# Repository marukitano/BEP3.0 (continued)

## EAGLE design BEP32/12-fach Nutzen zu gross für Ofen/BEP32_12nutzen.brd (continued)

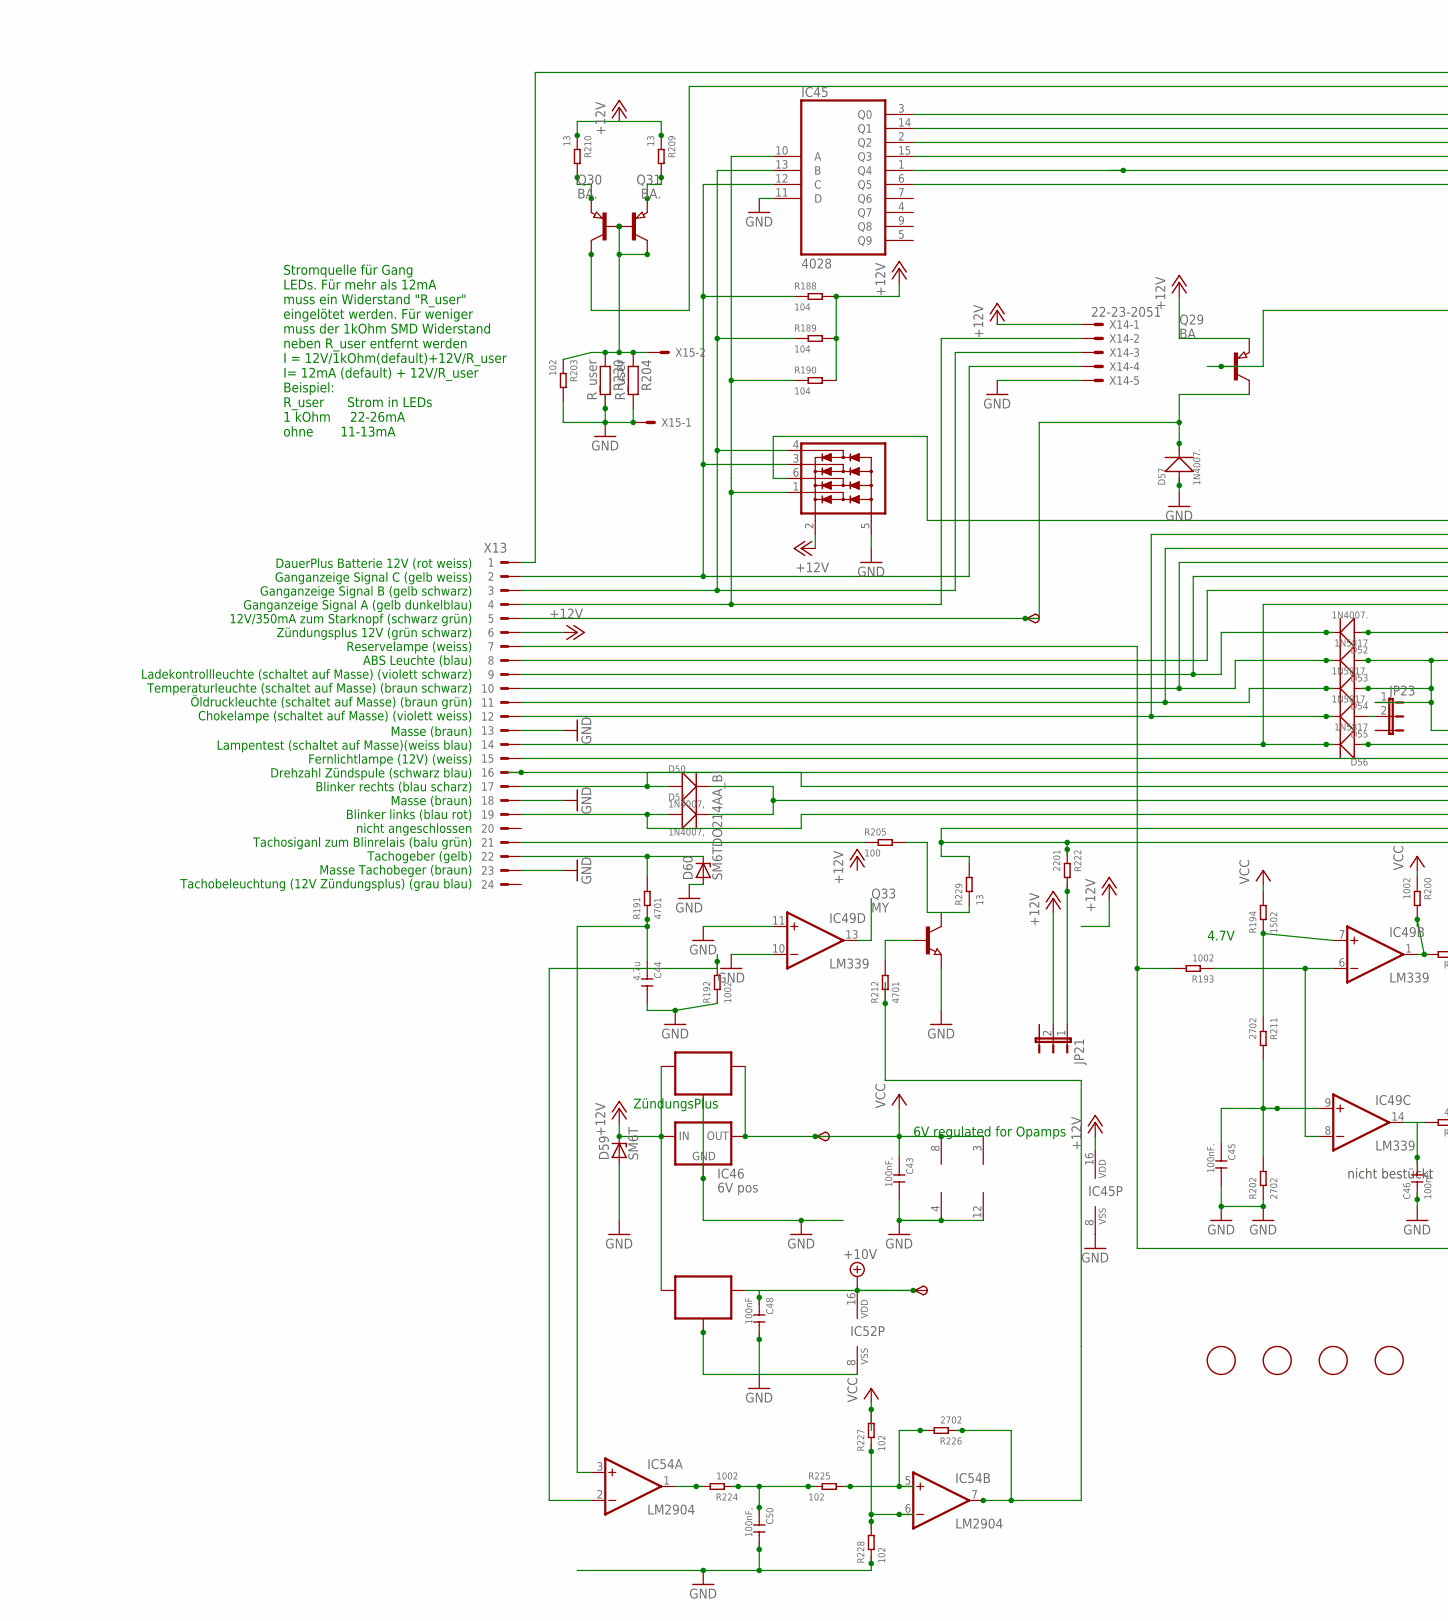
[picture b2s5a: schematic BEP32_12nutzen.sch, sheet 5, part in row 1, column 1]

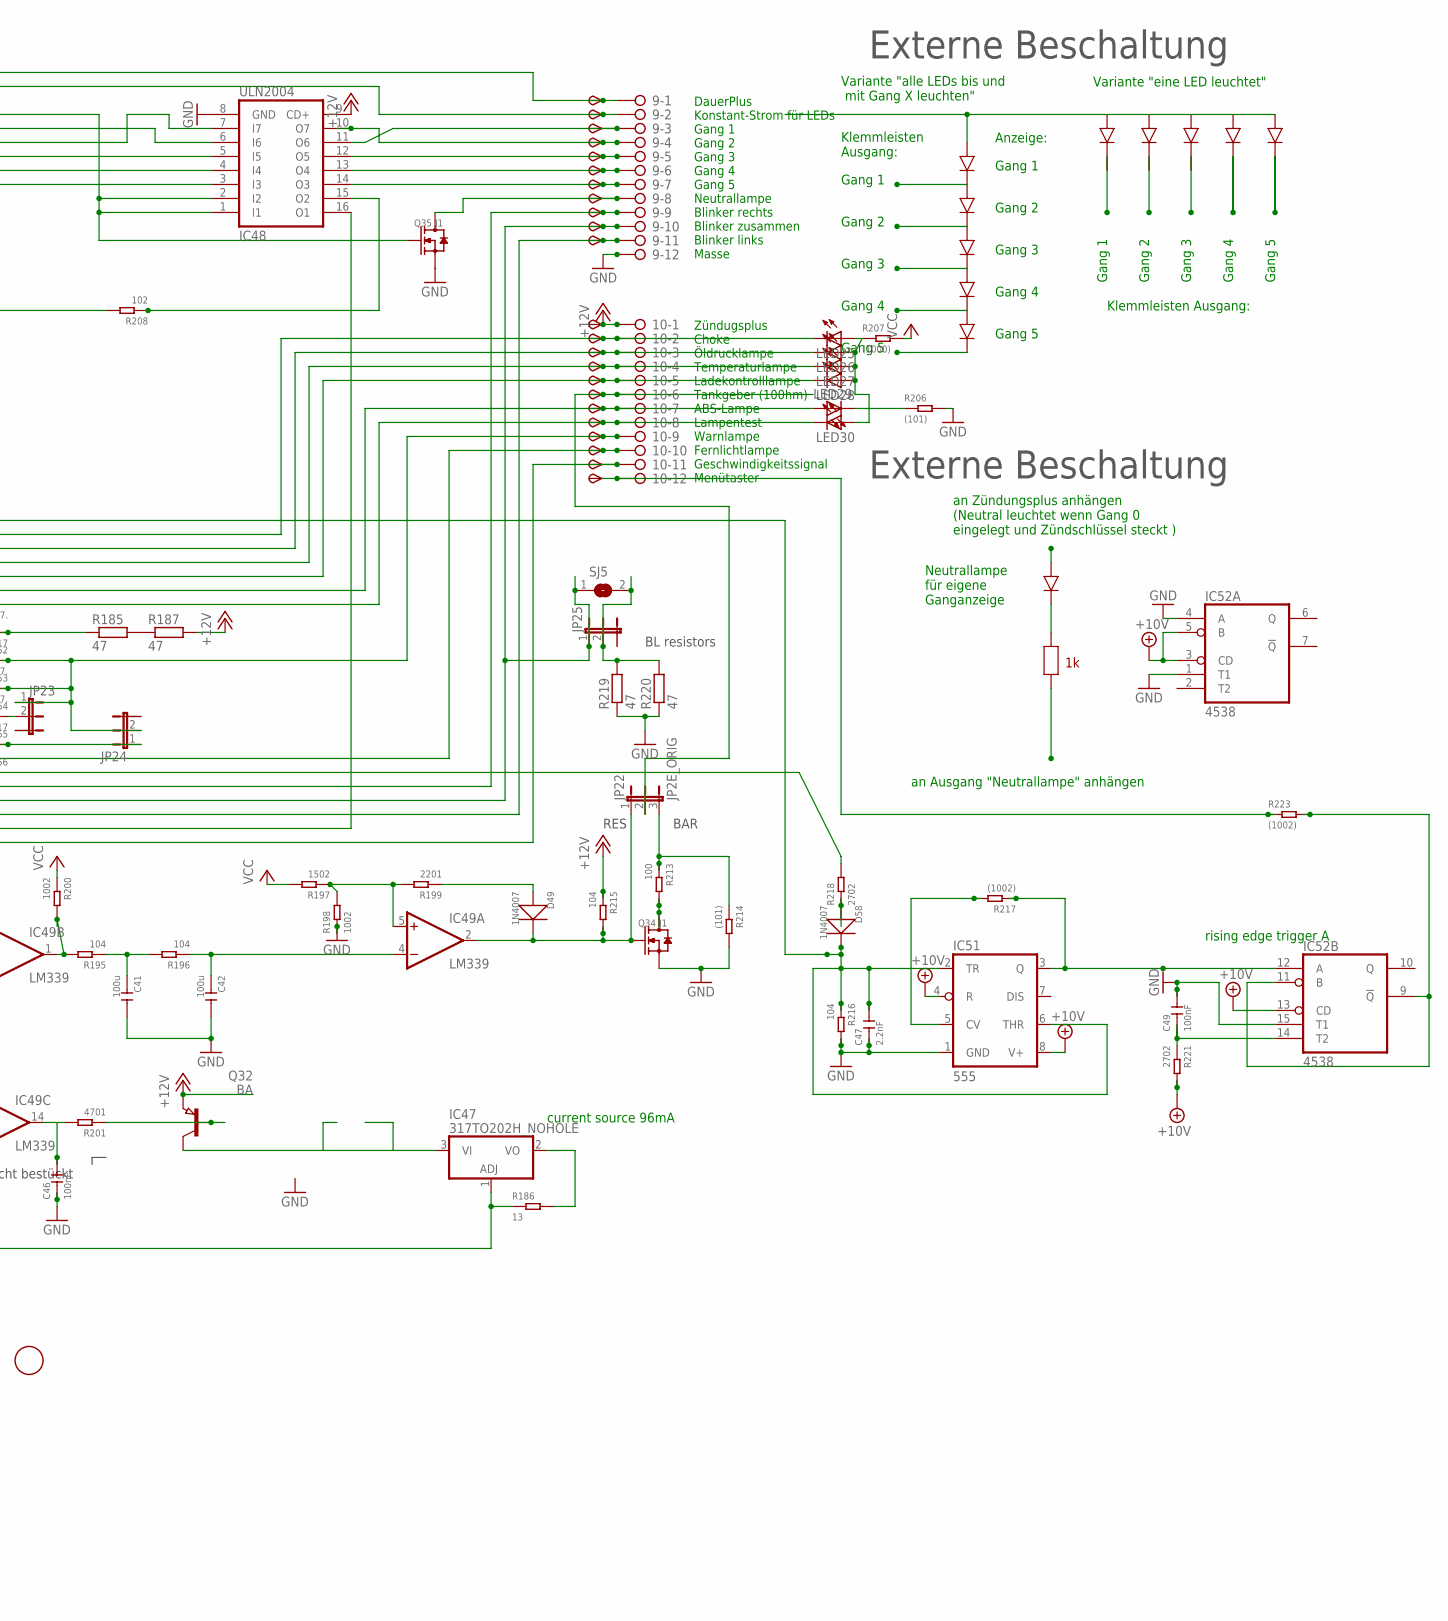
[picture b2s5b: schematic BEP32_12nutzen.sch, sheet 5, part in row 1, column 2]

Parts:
6V4, 10V4: TPSB2.0; B2.0
9, 10: 2081-1132; 12-PIN
C41, C42: 100u; C1206
C43, C50: 100nF,; C0805
C44: 4.7u; C0805
C45, C46: 100nF.; C0805
C47: 2.2nF; C0805
C48, C49: 100nF; C0805
D49, D58: 1N4007; DO-214AC
D50, D51: 1N4007,; DO-214AC
D52, D57: 1N4007.; DO-214AC
D53, D56: 1N5817; DO-214AC_SLIM
D54, D55: 1N5817.; DO-214AC_SLIM
D59: SM6T; DO214AA
D60: SM6TDO214AA_BI; DO214AA_BI
FID17, FID18, FID19, FID20: FIDUCIAL; FIDUCIAL_1MM
IC45: 4028; SO16
IC46: 6V pos; 78LXX
IC47: 317TO202H_NOHOLE; TO220H_NOHOLE
IC48: ULN2004; SO16
IC49: LM339; SO14
IC50: 78L06; SOT89_ROUND
IC51: 555; SO08
IC52: 4538; SO16
IC53: 78L10; SOT89_ROUND
IC54: LM2904; SO08
IC55: NUP4304SOT457_R; SOT457R_PHILIPS
JP21, JP23, JP24, JP25: JP2EJP2_SMALLPADS; JP2_SMALLPADS
JP22: JP2E_ORIG; JP2_ORIG_SMALLPADS
LED25, LED26, LED27, LED28, LED29, LED30: LEDLD260; LD260
Q29, Q32: BA; SOT89
Q30, Q31: BA.; SOT89
Q33: MY; SOT89
Q34, Q35: J1; SOT-23
R185, R187, R219, R220: 47; V235/17_1MM
R186, R209, R210, R229: 13; R1206
R188, R189, R190, R195, R196, R215, R216: 104; R0805
R191, R201, R212: 4701; R0805
R192, R193, R198, R200, R224: 1002; R0805
R194, R197: 1502; R0805
R199, R222: 2201; R0805
R202, R211, R218, R221, R226: 2702; R0805
R203, R208, R225, R227, R228: 102; R0805
R204, R230: R_user; R0805
R205, R213: 100; R0805
R206, R214: (101); R0805
R207: (1000); R0805
R217, R223: (1002); R0805
SJ5: SJ
START4: TPSB2.0; B2.0
TP93, TP94, TP95, TP96, TP97, TP98, TP99, TP100, TP101, TP102, TP103, TP104, TP105, TP106, TP107, TP108, TP109, TP110, TP112, TP113, TP114, TP115: TPSB2.0; B2.0
TP111: TPSB1,27; B1,27
X13: CON_BMWV2; 24-PIN_V2
X14: 22-23-2051
X15: 22-23-2021

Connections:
+10V: 10V4.TP, C48.1, IC51.4 (R), IC51.8 (V+), IC52.3 (CD), IC52.5 (B), IC52.13 (CD), IC52.16 (VDD), IC53.1 (OUT), R221.2; also elsewhere on the board
+12V: 10.1, D59.C, IC45.16 (VDD), IC46.IN, IC48.9 (CD+), IC50.3 (IN), IC53.3 (IN), IC55.2 (V+), JP21.2, Q29.3 (E), Q32.3 (E), R187.2, R188.2, R189.2, R190.2, R209.1, R210.1, R215.1, TP114.TP, X13.6, X14.1; also elsewhere on the board
+12V5: IC54.7 (OUT), R212.1, R226.1
GND: 9.12, C41.2, C42.2, C43.2, C44.2, C45.2, C46.1, C47.1, C48.2, C49.2, C50.2, D57.1 (+), D59.A, D60.A, IC45.8 (VSS), IC45.11 (D), IC46.GND, IC48.8 (GND), IC49.10 (-IN), IC49.11 (+IN), IC49.12 (GND), IC50.2 (GND), IC50.2@1 (GND), IC51.1 (GND), IC52.1 (T1), IC52.4 (A), IC52.8 (VSS), IC52.15 (T1), IC53.2 (GND), IC53.2@1 (GND), IC54.4 (V-), IC55.5 (V-), Q33.3 (E), Q34.2 (S), Q35.2 (S), R192.1, R198.1, R202.1, R203.2, R204.2, R206.2, R214.2, R216.2, R219.1, R220.1, R228.1, R230.2, X13.13, X13.18, X13.23, X14.5, X15.1; also elsewhere on the board
unnamed: R185.2, R187.1
unnamed: 10.9, D53.1 (+), D54.1 (+), JP23.1, JP24.2, TP111.TP
unnamed: IC45.10 (A), IC55.1 (D1), R190.1, X13.4, X14.2
unnamed: IC45.13 (B), IC55.4 (D4), R189.1, X13.3, X14.3
unnamed: D57.2 (-), Q29.2 (C), START4.TP, X13.5
unnamed: IC45.12 (C), IC55.3 (D3), R188.1, X13.2, X14.4
unnamed: 10.7, LED29.A, TP109.TP, X13.8
unnamed: 10.2, D55.2 (-), LED25.K (C), TP104.TP, X13.12
unnamed: 10.3, D54.2 (-), LED26.K (C), TP105.TP, X13.11
unnamed: 10.4, D53.2 (-), LED27.K (C), TP106.TP, X13.10
unnamed: 10.8, D56.2 (-), LED30.K (C), TP110.TP, X13.14
unnamed: 9.9, D50.1 (+), TP101.TP, X13.17
unnamed: 9.11, D51.1 (+), TP103.TP, X13.19
unnamed: D60.C, R191.2, X13.22
unnamed: C44.1, IC54.3 (+IN), R191.1
unnamed: 10.11, IC48.16 (O1), R222.1, R229.2, TP113.TP
unnamed: IC49.1 (OUT), R195.2, R200.2
unnamed: C41.1, R195.1, R196.2
unnamed: C42.1, IC49.4 (-IN), R196.1
unnamed: IC49.5 (+IN), R197.1, R198.2, R199.2
unnamed: D49.1 (+), R199.1
unnamed: C45.1, IC49.9 (+IN), R202.2, R211.2
unnamed: C46.2, IC49.14 (OUT), R201.2
unnamed: Q32.1 (B), R201.1
unnamed: IC45.2 (Q2), IC48.7 (I7)
unnamed: 9.5, IC48.12 (O5), TP97.TP
unnamed: IC45.1 (Q4), IC48.4 (I4)
unnamed: 9.8, Q35.3 (D), TP100.TP
unnamed: 10.10, TP112.TP, X13.15
unnamed: 10.5, D52.2 (-), LED28.K (C), TP107.TP, X13.9
unnamed: D52.1 (+), R185.1
unnamed: IC45.6 (Q5), IC48.3 (I3)
unnamed: 9.4, IC48.10 (O7), TP96.TP
unnamed: IC47.1 (ADJ), R186.1, R193.2, X13.7
unnamed: IC49.6 (-IN), IC49.8 (-IN), R193.1
unnamed: 9.2, Q31.2 (C), TP94.TP
unnamed: 9.1, TP93.TP, X13.1
unnamed: R218.2, X13.16
unnamed: IC45.15 (Q3), IC48.5 (I5)
unnamed: 9.6, IC48.13 (O4), TP98.TP
unnamed: 9.7, IC48.14 (O3), TP99.TP
unnamed: 10.6, JP22.2, TP108.TP
unnamed: LED29.K (C), R206.1
unnamed: LED25.A, LED26.A, LED27.A, LED28.A, LED30.A, R207.1
unnamed: Q29.1 (B), R208.2
unnamed: IC45.3 (Q0), IC48.1 (I1), IC48.2 (I2), Q35.1 (G)
unnamed: IC45.14 (Q1), IC48.6 (I6)
unnamed: 9.3, IC48.11 (O6), TP95.TP
unnamed: Q30.1 (B), Q30.2 (C), Q31.1 (B), R203.1, R204.1, R230.1, X15.2
unnamed: Q31.3 (E), R210.2
unnamed: Q30.3 (E), R209.2
unnamed: IC49.7 (+IN), R194.1, R211.1
unnamed: IC54.2 (-IN), R192.2
unnamed: Q33.1 (B), R212.2
unnamed: Q34.3 (D), R213.2
unnamed: IC47.2 (VO), R186.2
unnamed: IC47.3 (VI), Q32.2 (C)
unnamed: C47.2, D58.2 (-), IC51.2 (TR), IC51.6 (THR), IC55.6 (D2), R216.1
unnamed: IC51.5 (CV), R217.2
unnamed: IC51.3 (Q), IC52.12 (A), R217.1
unnamed: D58.1 (+), R218.1
unnamed: 9.10, D50.2 (-), D51.2 (-), JP25.1, SJ5.1, TP102.TP
unnamed: JP25.2, R219.2, R220.2, SJ5.2
unnamed: IC52.9 (!Q), IC52.11 (B), R223.2
unnamed: C49.1, IC52.14 (T2), R221.1
unnamed: JP21.1, R222.2
unnamed: IC48.15 (O2), R208.1
unnamed: 10.12, R223.1, TP115.TP
unnamed: D55.1 (+), JP23.2
unnamed: D49.2 (-), IC49.2 (OUT), JP22.1, Q34.1 (G), R215.2
unnamed: IC54.1 (OUT), R224.2
unnamed: C50.1, R224.1, R225.1
unnamed: IC54.5 (+IN), R225.2, R226.2
unnamed: IC54.6 (-IN), R227.1, R228.2
unnamed: D56.1 (+), JP24.1
unnamed: JP22.3, R213.1, R214.1
unnamed: R205.1, X13.21
unnamed: Q33.2 (C), R205.2, R229.1
VCC: 6V4.TP, C43.1, IC46.OUT, IC49.3 (V+), IC50.1 (OUT), IC54.8 (V+), R194.2, R197.2, R200.1, R207.2, R227.2; also elsewhere on the board

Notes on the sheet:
6V regulated for Opamps
current source 96mA
ZündungsPlus
Zündugsplus Choke Öldrucklampe Temperaturlampe Ladekontrolllampe Tankgeber (100hm) ABS-Lampe Lampentest Warnlampe Fernlichtlampe Geschwindigkeitssignal Menütaster
DauerPlus Konstant-Strom für LEDs Gang 1 Gang 2 Gang 3 Gang 4 Gang 5 Neutrallampe Blinker rechts Blinker zusammen Blinker links Masse
DauerPlus Batterie 12V (rot weiss) Ganganzeige Signal C (gelb weiss) Ganganzeige Signal B (gelb schwarz) Ganganzeige Signal A (gelb dunkelblau) 12V/350mA zum Starknopf (schwarz grün) Zündungsplus 12V (grün schwarz) Reservelampe (weiss) ABS Leuchte (blau) Ladekontrollleuchte (schaltet auf Masse) (vi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
Masse (braun) Lampentest (schaltet auf Masse)(weiss blau) Fernlichtlampe (12V) (weiss) Drehzahl Zündspule (schwarz blau) Blinker rechts (blau scharz) Masse (braun) Blinker links (blau rot) nicht angeschlossen Tachosiganl zum Blinrelais (balu grün) Tachogeber (gelb) Masse Tachobeger (braun) Tachobel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
4.7V
Stromquelle für Gang LEDs. Für mehr als 12mA muss ein Widerstand "R_user" eingelötet werden. Für weniger muss der 1kOhm SMD Widerstand neben R_user entfernt werden I = 12V/1kOhm(default)+12V/R_user I= 12mA (default) + 12V/R_user Beispiel: R_user Strom in LEDs 1 kOhm 22-26mA ohne 11-13mA
Gang 1
Gang 2
Gang 3
Gang 4
Gang 5
Variante "eine LED leuchtet"
Variante "alle LEDs bis und mit Gang X leuchten"
Klemmleisten Ausgang:
Klemmleisten Ausgang:
an Zündungsplus anhängen (Neutral leuchtet wenn Gang 0 eingelegt und Zündschlüssel steckt )
an Ausgang "Neutrallampe" anhängen
Neutrallampe für eigene Ganganzeige
Externe Beschaltung
Anzeige:
nicht bestückt
rising edge trigger A
BAR
RES
BL resistors

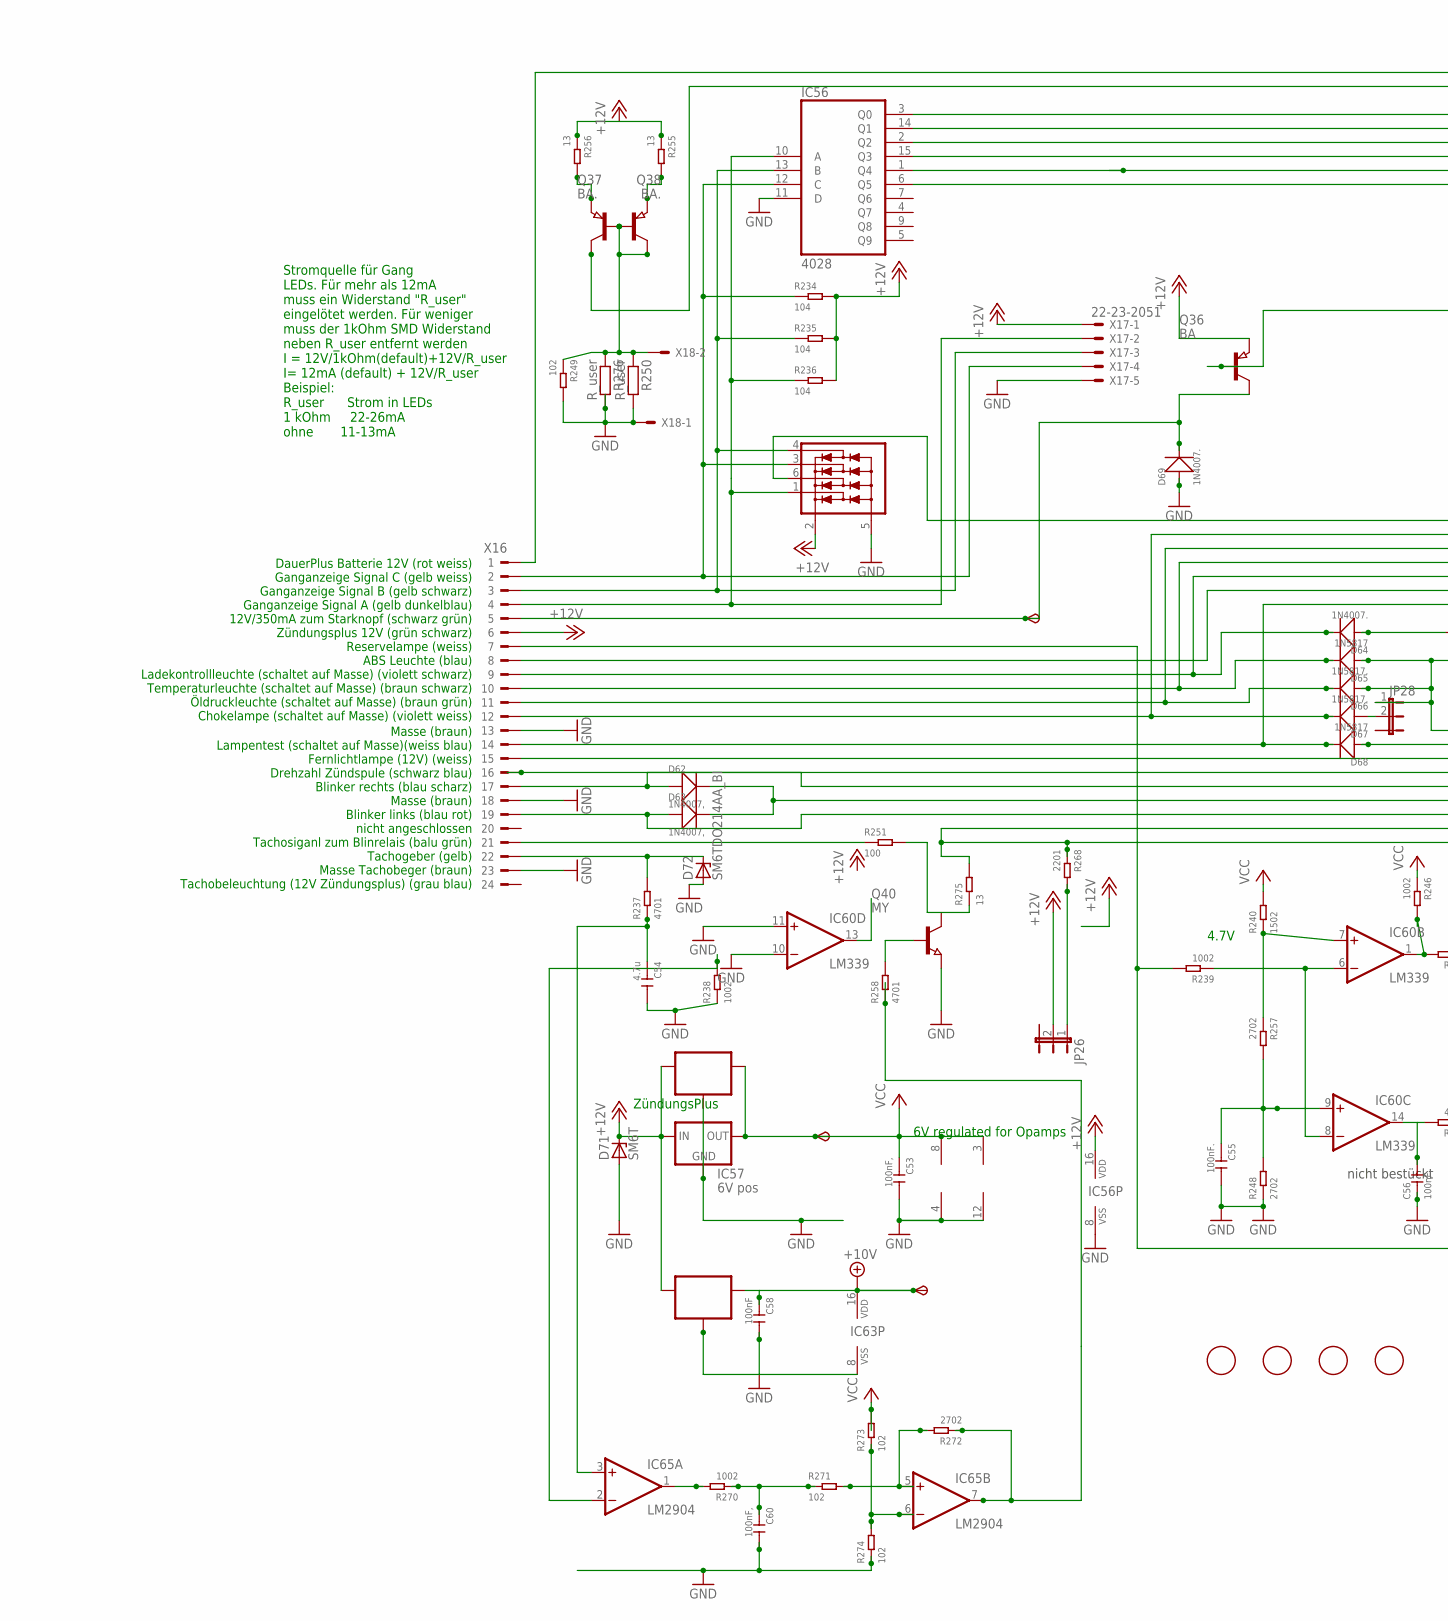
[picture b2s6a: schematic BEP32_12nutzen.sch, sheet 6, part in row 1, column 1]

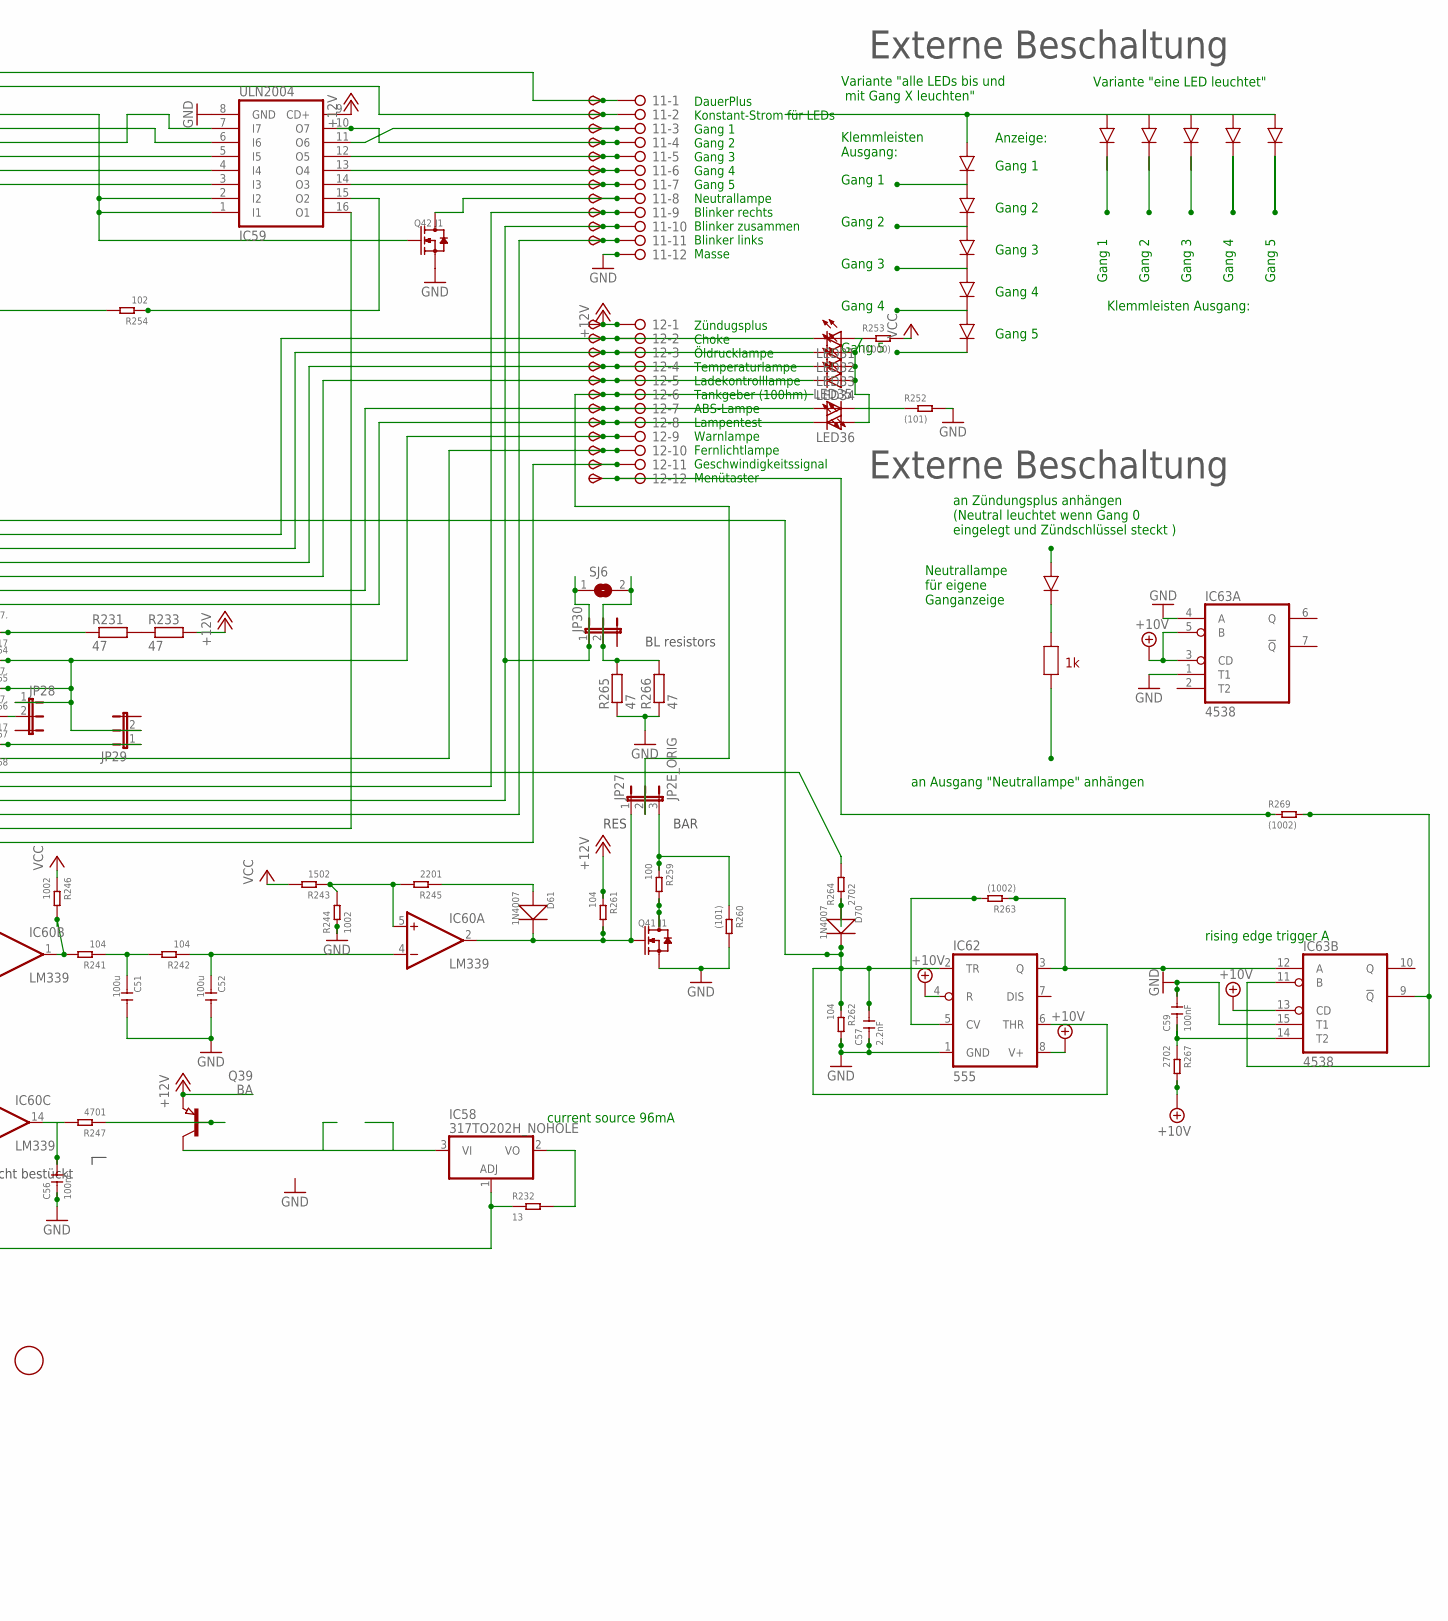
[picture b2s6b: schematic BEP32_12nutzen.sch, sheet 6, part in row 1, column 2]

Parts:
6V5, 10V5: TPSB2.0; B2.0
11, 12: 2081-1132; 12-PIN
C51, C52: 100u; C1206
C53, C60: 100nF,; C0805
C54: 4.7u; C0805
C55, C56: 100nF.; C0805
C57: 2.2nF; C0805
C58, C59: 100nF; C0805
D61, D70: 1N4007; DO-214AC
D62, D63: 1N4007,; DO-214AC
D64, D69: 1N4007.; DO-214AC
D65, D68: 1N5817; DO-214AC_SLIM
D66, D67: 1N5817.; DO-214AC_SLIM
D71: SM6T; DO214AA
D72: SM6TDO214AA_BI; DO214AA_BI
FID21, FID22, FID23, FID24: FIDUCIAL; FIDUCIAL_1MM
IC56: 4028; SO16
IC57: 6V pos; 78LXX
IC58: 317TO202H_NOHOLE; TO220H_NOHOLE
IC59: ULN2004; SO16
IC60: LM339; SO14
IC61: 78L06; SOT89_ROUND
IC62: 555; SO08
IC63: 4538; SO16
IC64: 78L10; SOT89_ROUND
IC65: LM2904; SO08
IC66: NUP4304SOT457_R; SOT457R_PHILIPS
JP26, JP28, JP29, JP30: JP2EJP2_SMALLPADS; JP2_SMALLPADS
JP27: JP2E_ORIG; JP2_ORIG_SMALLPADS
LED31, LED32, LED33, LED34, LED35, LED36: LEDLD260; LD260
Q36, Q39: BA; SOT89
Q37, Q38: BA.; SOT89
Q40: MY; SOT89
Q41, Q42: J1; SOT-23
R231, R233, R265, R266: 47; V235/17_1MM
R232, R255, R256, R275: 13; R1206
R234, R235, R236, R241, R242, R261, R262: 104; R0805
R237, R247, R258: 4701; R0805
R238, R239, R244, R246, R270: 1002; R0805
R240, R243: 1502; R0805
R245, R268: 2201; R0805
R248, R257, R264, R267, R272: 2702; R0805
R249, R254, R271, R273, R274: 102; R0805
R250, R276: R_user; R0805
R251, R259: 100; R0805
R252, R260: (101); R0805
R253: (1000); R0805
R263, R269: (1002); R0805
SJ6: SJ
START5: TPSB2.0; B2.0
TP116, TP117, TP118, TP119, TP120, TP121, TP122, TP123, TP124, TP125, TP126, TP127, TP128, TP129, TP130, TP131, TP132, TP133, TP135, TP136, TP137, TP138: TPSB2.0; B2.0
TP134: TPSB1,27; B1,27
X16: CON_BMWV2; 24-PIN_V2
X17: 22-23-2051
X18: 22-23-2021

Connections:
+10V: 10V5.TP, C58.1, IC62.4 (R), IC62.8 (V+), IC63.3 (CD), IC63.5 (B), IC63.13 (CD), IC63.16 (VDD), IC64.1 (OUT), R267.2; also elsewhere on the board
+12V: 12.1, D71.C, IC56.16 (VDD), IC57.IN, IC59.9 (CD+), IC61.3 (IN), IC64.3 (IN), IC66.2 (V+), JP26.2, Q36.3 (E), Q39.3 (E), R233.2, R234.2, R235.2, R236.2, R255.1, R256.1, R261.1, TP137.TP, X16.6, X17.1; also elsewhere on the board
+12V6: IC65.7 (OUT), R258.1, R272.1
GND: 11.12, C51.2, C52.2, C53.2, C54.2, C55.2, C56.1, C57.1, C58.2, C59.2, C60.2, D69.1 (+), D71.A, D72.A, IC56.8 (VSS), IC56.11 (D), IC57.GND, IC59.8 (GND), IC60.10 (-IN), IC60.11 (+IN), IC60.12 (GND), IC61.2 (GND), IC61.2@1 (GND), IC62.1 (GND), IC63.1 (T1), IC63.4 (A), IC63.8 (VSS), IC63.15 (T1), IC64.2 (GND), IC64.2@1 (GND), IC65.4 (V-), IC66.5 (V-), Q40.3 (E), Q41.2 (S), Q42.2 (S), R238.1, R244.1, R248.1, R249.2, R250.2, R252.2, R260.2, R262.2, R265.1, R266.1, R274.1, R276.2, X16.13, X16.18, X16.23, X17.5, X18.1; also elsewhere on the board
unnamed: R231.2, R233.1
unnamed: 12.9, D65.1 (+), D66.1 (+), JP28.1, JP29.2, TP134.TP
unnamed: IC56.10 (A), IC66.1 (D1), R236.1, X16.4, X17.2
unnamed: IC56.13 (B), IC66.4 (D4), R235.1, X16.3, X17.3
unnamed: D69.2 (-), Q36.2 (C), START5.TP, X16.5
unnamed: IC56.12 (C), IC66.3 (D3), R234.1, X16.2, X17.4
unnamed: 12.7, LED35.A, TP132.TP, X16.8
unnamed: 12.2, D67.2 (-), LED31.K (C), TP127.TP, X16.12
unnamed: 12.3, D66.2 (-), LED32.K (C), TP128.TP, X16.11
unnamed: 12.4, D65.2 (-), LED33.K (C), TP129.TP, X16.10
unnamed: 12.8, D68.2 (-), LED36.K (C), TP133.TP, X16.14
unnamed: 11.9, D62.1 (+), TP124.TP, X16.17
unnamed: 11.11, D63.1 (+), TP126.TP, X16.19
unnamed: D72.C, R237.2, X16.22
unnamed: C54.1, IC65.3 (+IN), R237.1
unnamed: 12.11, IC59.16 (O1), R268.1, R275.2, TP136.TP
unnamed: IC60.1 (OUT), R241.2, R246.2
unnamed: C51.1, R241.1, R242.2
unnamed: C52.1, IC60.4 (-IN), R242.1
unnamed: IC60.5 (+IN), R243.1, R244.2, R245.2
unnamed: D61.1 (+), R245.1
unnamed: C55.1, IC60.9 (+IN), R248.2, R257.2
unnamed: C56.2, IC60.14 (OUT), R247.2
unnamed: Q39.1 (B), R247.1
unnamed: IC56.2 (Q2), IC59.7 (I7)
unnamed: 11.5, IC59.12 (O5), TP120.TP
unnamed: IC56.1 (Q4), IC59.4 (I4)
unnamed: 11.8, Q42.3 (D), TP123.TP
unnamed: 12.10, TP135.TP, X16.15
unnamed: 12.5, D64.2 (-), LED34.K (C), TP130.TP, X16.9
unnamed: D64.1 (+), R231.1
unnamed: IC56.6 (Q5), IC59.3 (I3)
unnamed: 11.4, IC59.10 (O7), TP119.TP
unnamed: IC58.1 (ADJ), R232.1, R239.2, X16.7
unnamed: IC60.6 (-IN), IC60.8 (-IN), R239.1
unnamed: 11.2, Q38.2 (C), TP117.TP
unnamed: 11.1, TP116.TP, X16.1
unnamed: R264.2, X16.16
unnamed: IC56.15 (Q3), IC59.5 (I5)
unnamed: 11.6, IC59.13 (O4), TP121.TP
unnamed: 11.7, IC59.14 (O3), TP122.TP
unnamed: 12.6, JP27.2, TP131.TP
unnamed: LED35.K (C), R252.1
unnamed: LED31.A, LED32.A, LED33.A, LED34.A, LED36.A, R253.1
unnamed: Q36.1 (B), R254.2
unnamed: IC56.3 (Q0), IC59.1 (I1), IC59.2 (I2), Q42.1 (G)
unnamed: IC56.14 (Q1), IC59.6 (I6)
unnamed: 11.3, IC59.11 (O6), TP118.TP
unnamed: Q37.1 (B), Q37.2 (C), Q38.1 (B), R249.1, R250.1, R276.1, X18.2
unnamed: Q38.3 (E), R256.2
unnamed: Q37.3 (E), R255.2
unnamed: IC60.7 (+IN), R240.1, R257.1
unnamed: IC65.2 (-IN), R238.2
unnamed: Q40.1 (B), R258.2
unnamed: Q41.3 (D), R259.2
unnamed: IC58.2 (VO), R232.2
unnamed: IC58.3 (VI), Q39.2 (C)
unnamed: C57.2, D70.2 (-), IC62.2 (TR), IC62.6 (THR), IC66.6 (D2), R262.1
unnamed: IC62.5 (CV), R263.2
unnamed: IC62.3 (Q), IC63.12 (A), R263.1
unnamed: D70.1 (+), R264.1
unnamed: 11.10, D62.2 (-), D63.2 (-), JP30.1, SJ6.1, TP125.TP
unnamed: JP30.2, R265.2, R266.2, SJ6.2
unnamed: IC63.9 (!Q), IC63.11 (B), R269.2
unnamed: C59.1, IC63.14 (T2), R267.1
unnamed: JP26.1, R268.2
unnamed: IC59.15 (O2), R254.1
unnamed: 12.12, R269.1, TP138.TP
unnamed: D67.1 (+), JP28.2
unnamed: D61.2 (-), IC60.2 (OUT), JP27.1, Q41.1 (G), R261.2
unnamed: IC65.1 (OUT), R270.2
unnamed: C60.1, R270.1, R271.1
unnamed: IC65.5 (+IN), R271.2, R272.2
unnamed: IC65.6 (-IN), R273.1, R274.2
unnamed: D68.1 (+), JP29.1
unnamed: JP27.3, R259.1, R260.1
unnamed: R251.1, X16.21
unnamed: Q40.2 (C), R251.2, R275.1
VCC: 6V5.TP, C53.1, IC57.OUT, IC60.3 (V+), IC61.1 (OUT), IC65.8 (V+), R240.2, R243.2, R246.1, R253.2, R273.2; also elsewhere on the board

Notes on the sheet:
6V regulated for Opamps
current source 96mA
ZündungsPlus
Zündugsplus Choke Öldrucklampe Temperaturlampe Ladekontrolllampe Tankgeber (100hm) ABS-Lampe Lampentest Warnlampe Fernlichtlampe Geschwindigkeitssignal Menütaster
DauerPlus Konstant-Strom für LEDs Gang 1 Gang 2 Gang 3 Gang 4 Gang 5 Neutrallampe Blinker rechts Blinker zusammen Blinker links Masse
DauerPlus Batterie 12V (rot weiss) Ganganzeige Signal C (gelb weiss) Ganganzeige Signal B (gelb schwarz) Ganganzeige Signal A (gelb dunkelblau) 12V/350mA zum Starknopf (schwarz grün) Zündungsplus 12V (grün schwarz) Reservelampe (weiss) ABS Leuchte (blau) Ladekontrollleuchte (schaltet auf Masse) (vi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
Masse (braun) Lampentest (schaltet auf Masse)(weiss blau) Fernlichtlampe (12V) (weiss) Drehzahl Zündspule (schwarz blau) Blinker rechts (blau scharz) Masse (braun) Blinker links (blau rot) nicht angeschlossen Tachosiganl zum Blinrelais (balu grün) Tachogeber (gelb) Masse Tachobeger (braun) Tachobel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
4.7V
Stromquelle für Gang LEDs. Für mehr als 12mA muss ein Widerstand "R_user" eingelötet werden. Für weniger muss der 1kOhm SMD Widerstand neben R_user entfernt werden I = 12V/1kOhm(default)+12V/R_user I= 12mA (default) + 12V/R_user Beispiel: R_user Strom in LEDs 1 kOhm 22-26mA ohne 11-13mA
Gang 1
Gang 2
Gang 3
Gang 4
Gang 5
Variante "eine LED leuchtet"
Variante "alle LEDs bis und mit Gang X leuchten"
Klemmleisten Ausgang:
Klemmleisten Ausgang:
an Zündungsplus anhängen (Neutral leuchtet wenn Gang 0 eingelegt und Zündschlüssel steckt )
an Ausgang "Neutrallampe" anhängen
Neutrallampe für eigene Ganganzeige
Externe Beschaltung
Anzeige:
nicht bestückt
rising edge trigger A
BAR
RES
BL resistors
